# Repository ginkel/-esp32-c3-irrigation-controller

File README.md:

# ESP32-C3 Plant Watering Controller

A custom PCB for an ESP32-C3 based plant watering controller that features two channels to drive 12V water pumps and one input to check for low water level. If using esphome as [firmware](#firmware) it can be easily integrated into [Home Assistant](https://www.home-assistant.io/).

If you'd like to solder the PCB yourself, the smallest component to be soldered is 0603. The list of components and their placement is available as [interactive BOM](bom/ibom.html).

If you only need one channel (for a single pump), you can leave R5, R6, R11 D7, D9, Q2 and J3 unpopulated.

Documentation is probably far from complete. If you are missing a piece of the puzzle, feel free to open an issue or improve the documentation using a PR.

## Schematic

## BOM

| References     | Value                | LCSC part # |
|----------------|----------------------|-------------|
| C1             | 10nF                 | C57112      |
| C2             | 10uF                 | C15849      |
| C3             | 10uF                 | C89632      |
| C4             | 10uF                 | C336204     |
| C5             | 150uF                | C242120     |
| C6, C8         | 100nF                | C1591       |
| C7             | 1uF                  | C15849      |
| C9             | 10uF                 | C194427     |
| R2, R7, R8, R9 | 10k                  | C25804      |
| R3, R6         | 1k                   | C21190      |
| R4, R5, R13    | 47k                  | C25819      |
| R10, R11       | 100                  | C22775      |
| R12, R14       | 27                   | C863706     |
| R15, R16       | 5.1k                 | C23186      |
| R1             | 5.9k                 | C23071      |
| L1             | 68uH                 | C694542     |
| D1             | PMEG6010CEH,115      | C110797     |
| D2             | SMAJ15CA             | C110044     |
| D3             | SS52                 | C727051     |
| D4             | B5819W SL            | C8598       |
| D5             | CUS10S30,H3F         | C146335     |
| D6, D7         | LED                  | C434419     |
| D8, D9         | SS56                 | C2904059    |
| D10            | LC03CI               | C384865     |
| U1             | TPS5430DDA           | C9864       |
| U2             | AMS1117-3.3          | C347222     |
| U3             | SRV05-4              | C85364      |
| U4             | ESP32-C3-WROOM-02    | C2934560    |
| F1             | BSMD1812-200-24V     | C206993     |
| SW1, SW2       | XUNPU TS-1089S-02526 | C455282     |
| Q1, Q2         | IRF7401              | C5346818    |
| J1, J2, J3     | DB128L-5.08-2P-GN-P  | C430600     |
| J4             | USB-C Connector      | C165948     |
| J5             | DB125-2.54-2P-GN-S   | C918120     |

I am sourcing my components from LCSC. If you also do, the LCSC part # may be helpful.

## External Parts

For a full-fledged plant watering solution you'll need some additional components/parts. Links go to AliExpress, but you can of course source the components from other sources if you prefer a different suppliers.

* [Submersible 12V water pump](https://aliexpress.com/item/1005005489175847.html)
* [Water level sensor](https://aliexpress.com/item/1005004306055007.html)
* [Water filter (8mm)](https://aliexpress.com/item/1005005032983727.html)
* [Sprinklers](https://aliexpress.com/item/1005004917374250.html)
* [8mm to 4mm connector](https://aliexpress.com/item/1005004875653640.html)
* 8mm hose
* 4mm hose
* Water reservoir, e.g., IKEA HÅLLBAR (35 l)

## Firmware

The firmware I am running on the controller is based on [esphome](https://esphome.io/). I am using the following snippet (for a single channel and a moisture sensor named `sensor.plant_herbs_balcony_soil_moisture`), which you'll probably want to customize to integrate with your Home Assistant instance and WiFi.

```
globals:
  - id: last_run
    type: time_t
    restore_value: yes
    initial_value: '0'

esphome:
  name: plant-watering
  name_add_mac_suffix: true
  friendly_name: ESP32-C3 Plant Watering Controller
  platformio_options:
    board_build.flash_mode: dio
    board_build.f_flash: 40000000L
    board_build.flash_size: 4MB
    # run with 80 MHz
    board_build.f_cpu: 80000000L

esp32:
  board: esp32-c3-devkitm-1
  framework:
    type: esp-idf
    sdkconfig_options:
      CONFIG_COMPILER_OPTIMIZATION_SIZE: y
  variant: esp32c3

mqtt:
  broker: [...]
  username: [...]
  password: [...]
  on_message:
    - topic: esphome/plant_watering/pump1
      payload: 'ON'
      then:
        - if:
            condition:
              binary_sensor.is_on: water_level
            then:
              - globals.set:
                  id: last_run
                  value: !lambda 'return id(homeassistant_time).now().timestamp;'
              - logger.log: "Turning irrigation 'pump1' on"
              - output.turn_on: pump1
              - logger.log: "Waiting 20s"
              - delay: 20s
              - logger.log: "Turning irrigation 'pump1' off"
              - output.turn_off: pump1
            else:
              - logger.log: "Water level is critical - refusing to turn on irrigation"

output:
  - platform: gpio
    pin:
      number: GPIO5
      mode:
        output: true
        pulldown: true
      drive_strength: 5mA
    id: pump1
  - platform: gpio
    pin:
      number: GPIO6
      mode:
        output: true
        pulldown: true
      drive_strength: 5mA
    id: pump2

binary_sensor:
  - platform: gpio
    pin:
      number: GPIO4
      mode:
        input: true
      inverted: false
    name: "Water Level"
    id: water_level
    filters:
      - delayed_on: 1s
      - delayed_off: 1s
    on_release:
      then:
        - logger.log: "Water level critical - turning off all pumps"
        - output.turn_off: pump1
        - output.turn_off: pump2

sensor:
  - platform: uptime
    name: "ESP32-C3 Plant Watering Controller Uptime"

  - platform: wifi_signal
    name: "ESP32-C3 Plant Watering Controller WiFi Signal"
    update_interval: 15s

  - platform: homeassistant
    name: "Soil humidity"
    entity_id: sensor.plant_herbs_balcony_soil_moisture
    id: plant_herbs_balcony_soil_moisture

text_sensor:
  - platform: template
    name: "ESP32-C3 Plant Watering Controller Last Run"
    icon: mdi:clock-start
    lambda: |-
      return ESPTime::from_epoch_local(id(last_run)).strftime("%Y-%m-%dT%H:%M:%S");
    update_interval: 60s

time:
  - platform: homeassistant
    id: homeassistant_time
    on_time:
      - cron: '00 /5 18-6 * * *'
        then:
        - if:
            condition:
              and:
                - binary_sensor.is_on: water_level
                - lambda: |-
                    return id(plant_herbs_balcony_soil_moisture).state < 55;
                - lambda: |-
                    return id(homeassistant_time).now().is_valid() && (id(homeassistant_time).now().timestamp - id(last_run) > 43200);
            then:
              - globals.set:
                  id: last_run
                  value: !lambda 'return id(homeassistant_time).now().timestamp;'
              - logger.log: "Turning irrigation 'pump1' on"
              - output.turn_on: pump1
              - logger.log: "Waiting 20s"
              - delay: 20s
              - logger.log: "Turning irrigation 'pump1' off"
              - output.turn_off: pump1
            else:
              - logger.log:
                  format: "Water level: %d, average soil moisture: %.1f - refusing to water plants"
                  args: ['id(water_level).state', 'id(weighted_soil_moisture).state']
```

## Integration

The PCB does not offer a built-in mechanism to measure soil humidity, but the [b-parasite](https://github.com/rbaron/b-parasite) open source project provides a suitable DIY capacitive soil moisture sensor that can easily be integrated using ZigBee / Home Assistant.

## Action Shots

## License
The hardware and associated design files are released under the [Creative Commons CC BY-SA 4.0 license](https://creativecommons.org/licenses/by-sa/4.0/).

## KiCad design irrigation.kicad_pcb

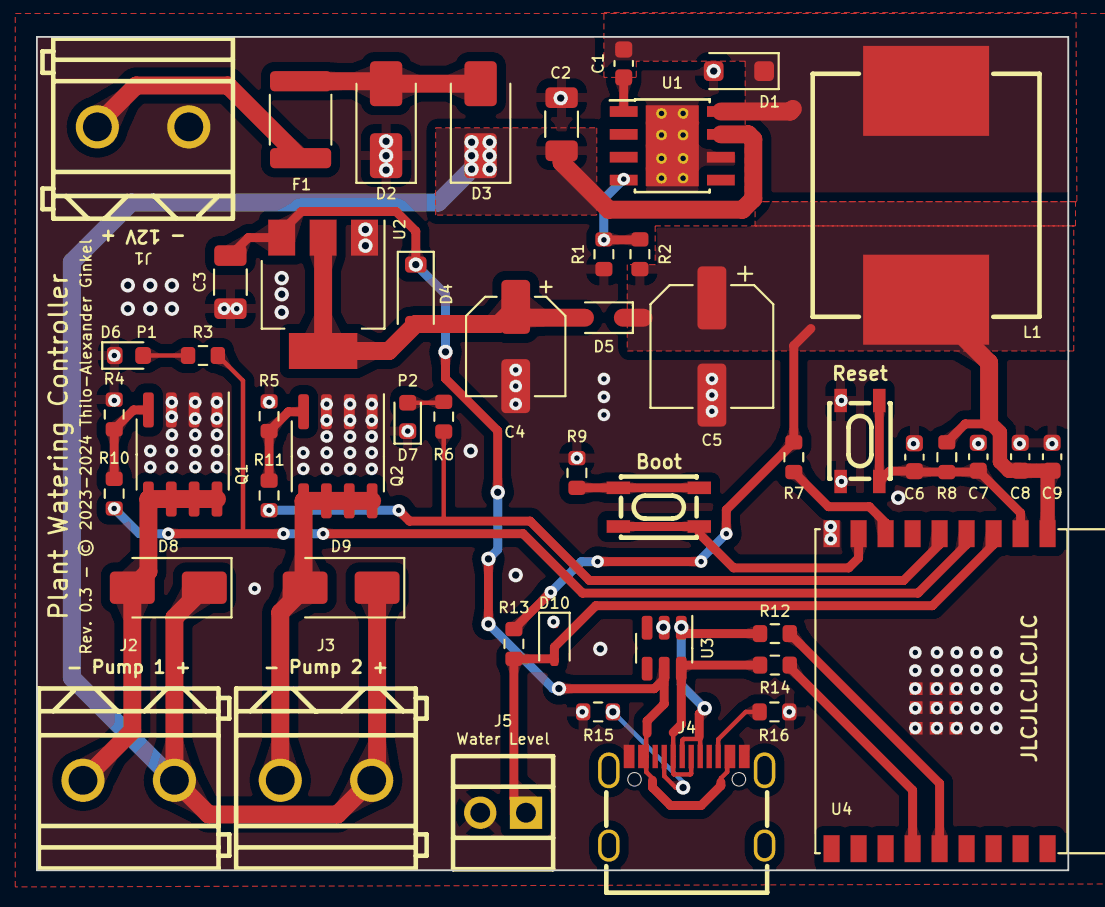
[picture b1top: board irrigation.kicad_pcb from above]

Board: 2 copper layers, 57.3 x 46.3 mm, 50 parts (0 on the bottom side), 29 nets.

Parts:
C1: 10nF; C_0603_1608Metric
C2, C3: 10uF; C_1206_3216Metric
C4: 10uF; CP_Elec_5x5.8
C5: 150uF; CP_Elec_6.3x7.7
C6, C8: 100nF; C_0603_1608Metric
C7: 1uF; C_0603_1608Metric
C9: 10uF; C_0603_1608Metric
D1: PMEG6010CEH,115; D_SOD-123F
D2: SMAJ15CA; D_SMA
D3: SS52; D_SMA
D4: B5819W SL; D_SOD-123
D5: CUS10S30,H3F; D_SOD-323
D6, D7: LED; LED_0603_1608Metric
D8, D9: SS56; D_SMA
D10: LC03CI; D_SOD-323
F1: BSMD1812-200-24V; Fuse_1812_4532Metric
J1: - 12V +; CONN-TH_2P-P5.08_DB128L-5.08-2P-GN-P
J2: - Pump 1 +; CONN-TH_2P-P5.08_DB128L-5.08-2P-GN-P
J3: - Pump 2 +; CONN-TH_2P-P5.08_DB128L-5.08-2P-GN-P
J4: USB_C_Receptacle_USB2.0; USB-C_SMD-TYPE-C-31-M-12
J5: Water Level; CONN-TH_DB125-2.54-2P-GN
L1: 68uH; IND-SMD_L12.6-W13.5
Q1, Q2: IRF7401; SOIC-8_3.9x4.9mm_P1.27mm
R1: 5.9k; R_0603_1608Metric
R2, R7, R8, R9: 10k; R_0603_1608Metric
R3, R6: 1k; R_0603_1608Metric
R4, R5, R13: 47k; R_0603_1608Metric
R10, R11: 100; R_0603_1608Metric
R12, R14: 27; R_0603_1608Metric
R15, R16: 5.1k; R_0603_1608Metric
SW1: Reset; SW-SMD_4P-L4.2-W3.3-P2.15-LS5.1
SW2: Boot; SW-SMD_4P-L4.2-W3.3-P2.15-LS5.1
U1: TPS5430DDA; TI_SO-PowerPAD-8_ThermalVias
U2: AMS1117-3.3; SOT-223-3_TabPin2
U3: SRV05-4; SOT-23-6
U4: ESP32-C3-WROOM-02

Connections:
+3V3: C5.1, C8.1, C9.1, D5.1 (K), L1.2, R2.1, R7.1, R8.1, R13.2, U4.1 (3V3)
+12V: C2.1, D3.1 (K), D8.1 (K), D9.1 (K), J2.1, J3.1, U1.7 (VIN)
/EN: C6.2, C7.1, R8.2, SW1.3 (K), SW1.4 (A), U4.2 (EN/CHIP_PU)
/GPIO4: D10.2 (A2), J5.1, R13.1, U4.3 (GPIO4/ADC1_CH4)
/GPIO5: R3.1, R10.1, U4.4 (GPIO5/ADC2_CH0)
/GPIO6: R6.1, R11.1, U4.5 (GPIO6)
/USB_D+: J4.A6 (D+), J4.B6 (D+), R12.2, U3.1 (IO1)
/USB_D-: J4.A7 (D-), J4.B7 (D-), R14.2, U3.6 (IO4)
/USB_VBUS: C3.1, D4.1 (K), J4.A4 (VBUS), J4.A9 (VBUS), J4.B4 (VBUS), J4.B9 (VBUS), U2.3 (VI), U3.5 (VP)
GND: C2.2, C3.2, C4.2, C5.2, C6.1, C7.2, C8.2, C9.2, D1.2 (A), D2.1 (A1), D6.1 (K), D7.1 (K), D10.1 (A1), J1.2, J4.A1 (GND), J4.A12 (GND), J4.B1 (GND), J4.B12 (GND), J5.2, Q1.1 (S), Q1.2 (S), Q1.3 (S), Q2.1 (S), Q2.2 (S), Q2.3 (S), R1.1, R4.2, R5.2, R9.2, R15.2, R16.2, SW1.1, SW1.2, U1.6 (GND), U1.9 (GNDPAD), U2.1 (GND), U3.2 (VN), U4.9 (GND), U4.19 (GND)
unnamed: C1.2, D1.1 (K), L1.1, U1.8 (PH)
unnamed: D2.2 (A2), D3.2 (A), F1.2
unnamed: C4.1, D4.2 (A), D5.2 (A), U2.2 (VO)
unnamed: D6.2 (A), R3.2
unnamed: D7.2 (A), R6.2
unnamed: D8.2 (A), J2.2, Q1.5 (D), Q1.6 (D), Q1.7 (D), Q1.8 (D)
unnamed: D9.2 (A), J3.2, Q2.5 (D), Q2.6 (D), Q2.7 (D), Q2.8 (D)
unnamed: F1.1, J1.1
unnamed: J4.A5 (CC1), R15.1
unnamed: J4.B5 (CC2), R16.1
unnamed: Q1.4 (G), R4.1, R10.2
unnamed: Q2.4 (G), R5.1, R11.2
unnamed: R9.1, SW2.1, SW2.2
unnamed: SW2.3 (K), SW2.4 (A), U4.8 (GPIO9)
unnamed: C1.1, U1.1 (BOOT)
unnamed: R1.2, R2.2, U1.4 (VSENSE)
unnamed: R7.2, U4.7 (GPIO8)
unnamed: R14.1, U4.13 (GPIO18/USB_D-)
unnamed: R12.1, U4.14 (GPIO19/USB_D+)

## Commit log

2023-06-26 Initial import
2023-06-26 Various bug fixes & improvements
2023-06-27 Add interactive BOM
2023-06-27 Cleanup iBOM
2023-09-05 Downgrade KiCad version
2024-05-12 Add documentation
2024-05-12 License
2024-05-12 Add disclaimer
2024-05-12 Add BOM, fix nets
2024-05-12 Update PCB & gerber files
2024-05-12 Add action shots

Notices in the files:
irrigation.kicad_pcb:
Rev. 0.3 - © 2023-2024 Thilo-Alexander Ginkel
